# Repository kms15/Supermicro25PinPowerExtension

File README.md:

# Supermicro 25 Pin Power Extension

This project is an extension cable for a Super Micro PWS-1K66P-1R power supply.
This power supply has a 40mm fan which is quite loud, but the design of many
servers does not leave enough space around the power supply to replace this fan
with a larger (and quieter) fan.  The connector on this power supply is a
proprietary 2x25 contact PCB edge connector that carries high (133 Amp)
currents, and thus needs a custom extension cable to move the power supply out
of the case to somewhere with more space.

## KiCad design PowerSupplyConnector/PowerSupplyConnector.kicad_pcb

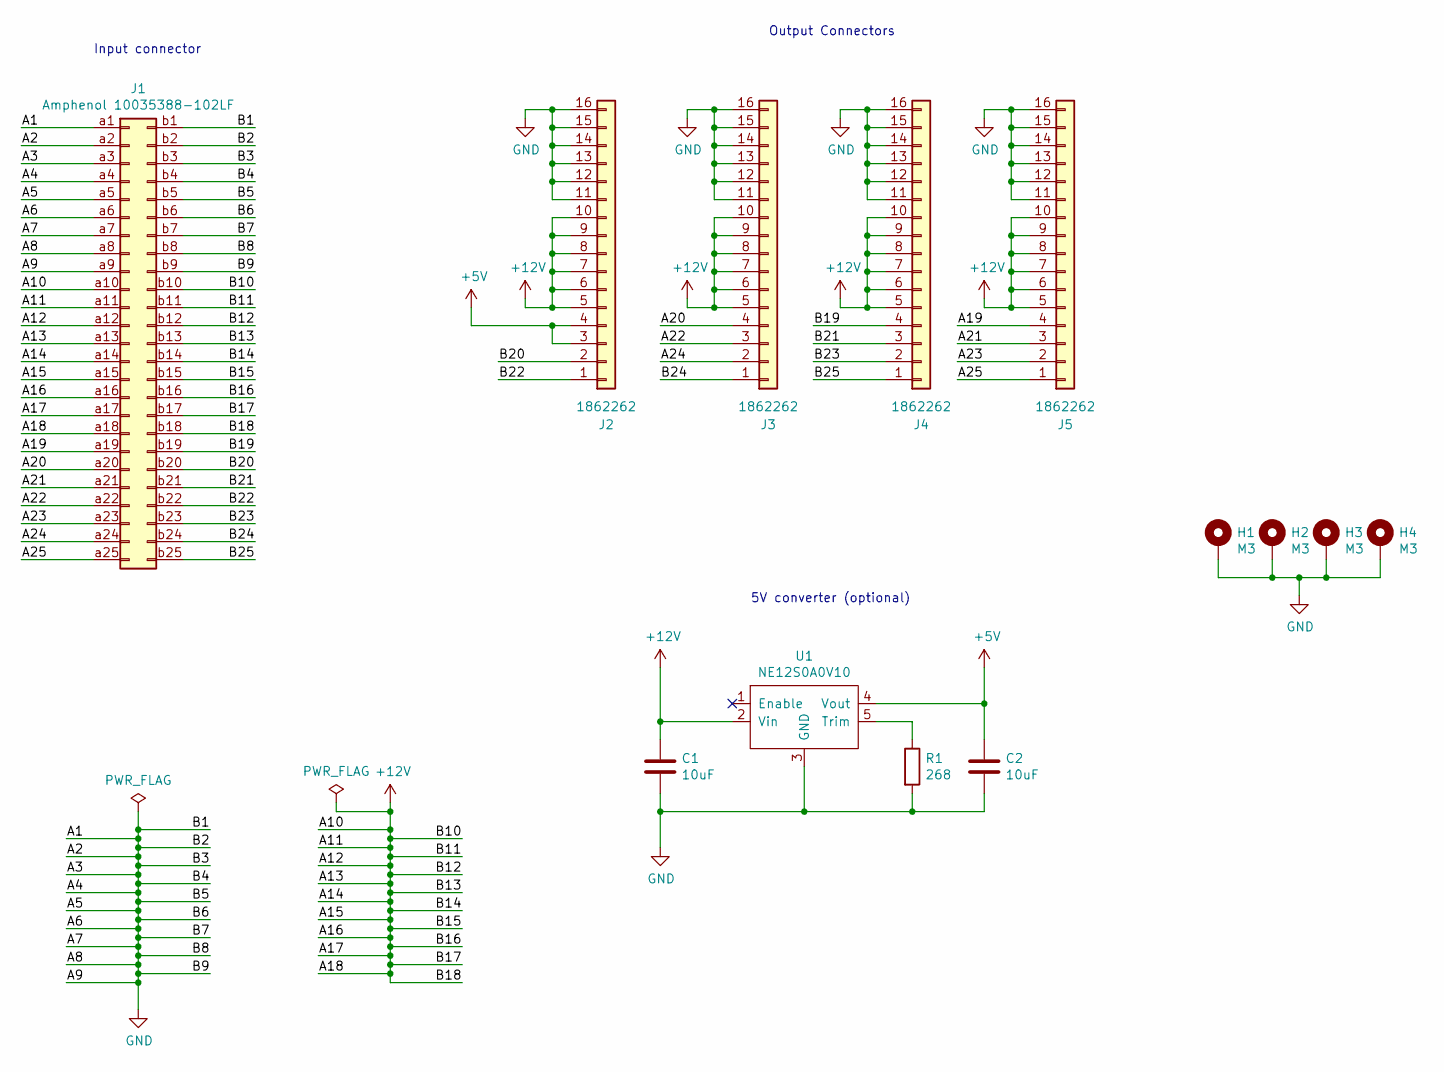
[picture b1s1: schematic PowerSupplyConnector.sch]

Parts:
C1, C2: 10uF; C_0603_1608Metric
H1, H2, H3, H4: M3; MountingHole_3.2mm_M3_Pad
J1: Amphenol 10035388-102LF; Amphenol_10035388-102LF
J2, J3, J4, J5: 1862262; PhoenixContact1862262
R1: 268; R_0603_1608Metric
U1: NE12S0A0V10; Delta_NE12S0A0V10

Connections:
+5V: C2.1, J2.3, J2.4, U1.4 (Vout)
+12V: C1.1, J1.a10, J1.a11, J1.a12, J1.a13, J1.a14, J1.a15, J1.a16, J1.a17, J1.a18, J1.b10, J1.b11, J1.b12, J1.b13, J1.b14, J1.b15, J1.b16, J1.b17, J1.b18, J2.5, J2.6, J2.7, J2.8, J2.9, J2.10, J3.5, J3.6, J3.7, J3.8, J3.9, J3.10, J4.5, J4.6, J4.7, J4.8, J4.9, J4.10, J5.5, J5.6, J5.7, J5.8, J5.9, J5.10, U1.2 (Vin)
/A19: J1.a19, J5.4
/A20: J1.a20, J3.4
/A21: J1.a21, J5.3
/A22: J1.a22, J3.3
/A23: J1.a23, J5.2
/A24: J1.a24, J3.2
/A25: J1.a25, J5.1
/B19: J1.b19, J4.4
/B20: J1.b20, J2.2
/B21: J1.b21, J4.3
/B22: J1.b22, J2.1
/B23: J1.b23, J4.2
/B24: J1.b24, J3.1
/B25: J1.b25, J4.1
GND: C1.2, C2.2, H1.1, H2.1, H3.1, H4.1, J1.a1, J1.a2, J1.a3, J1.a4, J1.a5, J1.a6, J1.a7, J1.a8, J1.a9, J1.b1, J1.b2, J1.b3, J1.b4, J1.b5, J1.b6, J1.b7, J1.b8, J1.b9, J2.11, J2.12, J2.13, J2.14, J2.15, J2.16, J3.11, J3.12, J3.13, J3.14, J3.15, J3.16, J4.11, J4.12, J4.13, J4.14, J4.15, J4.16, J5.11, J5.12, J5.13, J5.14, J5.15, J5.16, R1.2, U1.3 (GND)
unnamed: R1.1, U1.5 (Trim)

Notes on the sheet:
Input connector
Output Connectors
5V converter (optional)

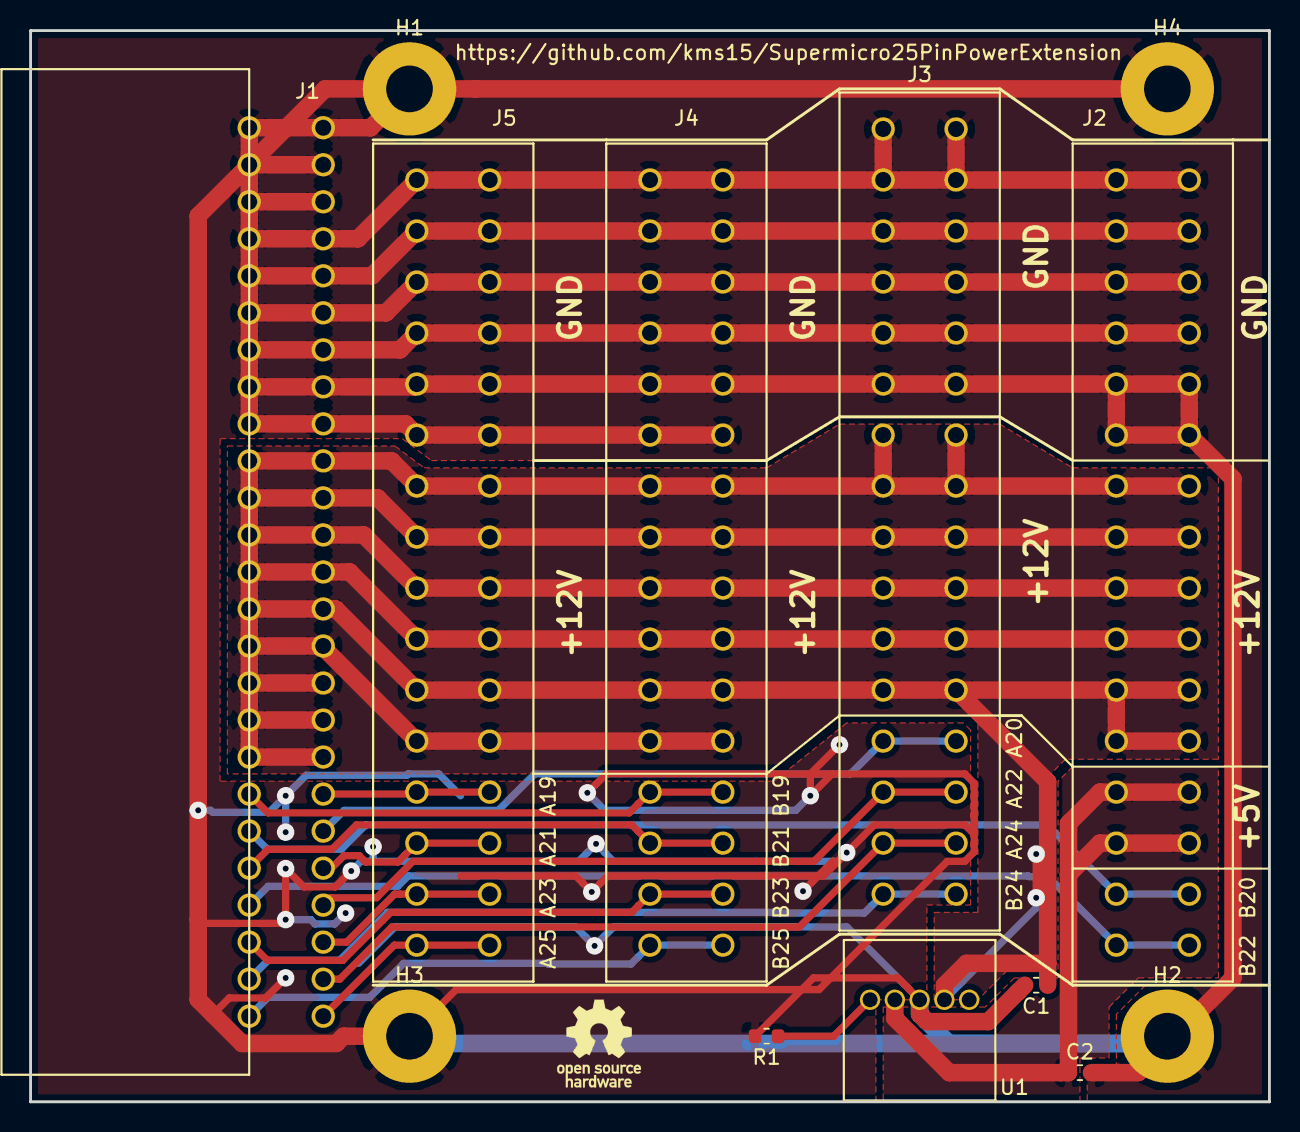
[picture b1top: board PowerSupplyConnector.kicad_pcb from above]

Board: 2 copper layers, 85.0 x 73.5 mm, 13 parts (0 on the bottom side), 18 nets.

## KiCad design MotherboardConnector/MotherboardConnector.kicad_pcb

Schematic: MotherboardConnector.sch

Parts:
C1, C2: 10uF; C_0603_1608Metric
H1, H2, H3, H4: MountingHole_Pad; MountingHole_3.2mm_M3_Pad
J1: Amphenol 10035388-102LF PCB edge; Amphenol_10035388-102LF_PCB_Edge
J2, J3, J4, J5: 1862262; PhoenixContact1862262
R1: 268; R_0603_1608Metric
U1: NE12S0A0V10PNF; Delta_NE12S0A0V10

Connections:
+5V: C2.1, J2.13, J2.14, U1.4
+12V: C1.1, J1.a10, J1.a11, J1.a12, J1.a13, J1.a14, J1.a15, J1.a16, J1.a17, J1.a18, J1.b10, J1.b11, J1.b12, J1.b13, J1.b14, J1.b15, J1.b16, J1.b17, J1.b18, J2.7, J2.8, J2.9, J2.10, J2.11, J2.12, J3.7, J3.8, J3.9, J3.10, J3.11, J3.12, J4.7, J4.8, J4.9, J4.10, J4.11, J4.12, J5.7, J5.8, J5.9, J5.10, J5.11, J5.12, U1.2
/A19: J1.a19, J5.13
/A20: J1.a20, J3.13
/A21: J1.a21, J5.14
/A22: J1.a22, J3.14
/A23: J1.a23, J5.15
/A24: J1.a24, J3.15
/A25: J1.a25, J5.16
/B19: J1.b19, J4.13
/B20: J1.b20, J2.15
/B21: J1.b21, J4.14
/B22: J1.b22, J2.16
/B23: J1.b23, J4.15
/B24: J1.b24, J3.16
/B25: J1.b25, J4.16
GND: C1.2, C2.2, H1.1, H2.1, H3.1, H4.1, J1.a1, J1.a2, J1.a3, J1.a4, J1.a5, J1.a6, J1.a7, J1.a8, J1.a9, J1.b1, J1.b2, J1.b3, J1.b4, J1.b5, J1.b6, J1.b7, J1.b8, J1.b9, J2.1, J2.2, J2.3, J2.4, J2.5, J2.6, J3.1, J3.2, J3.3, J3.4, J3.5, J3.6, J4.1, J4.2, J4.3, J4.4, J4.5, J4.6, J5.1, J5.2, J5.3, J5.4, J5.5, J5.6, R1.2, U1.3
unnamed: R1.1, U1.5

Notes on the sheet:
Output connector
Input Connectors
5V converter (optional)

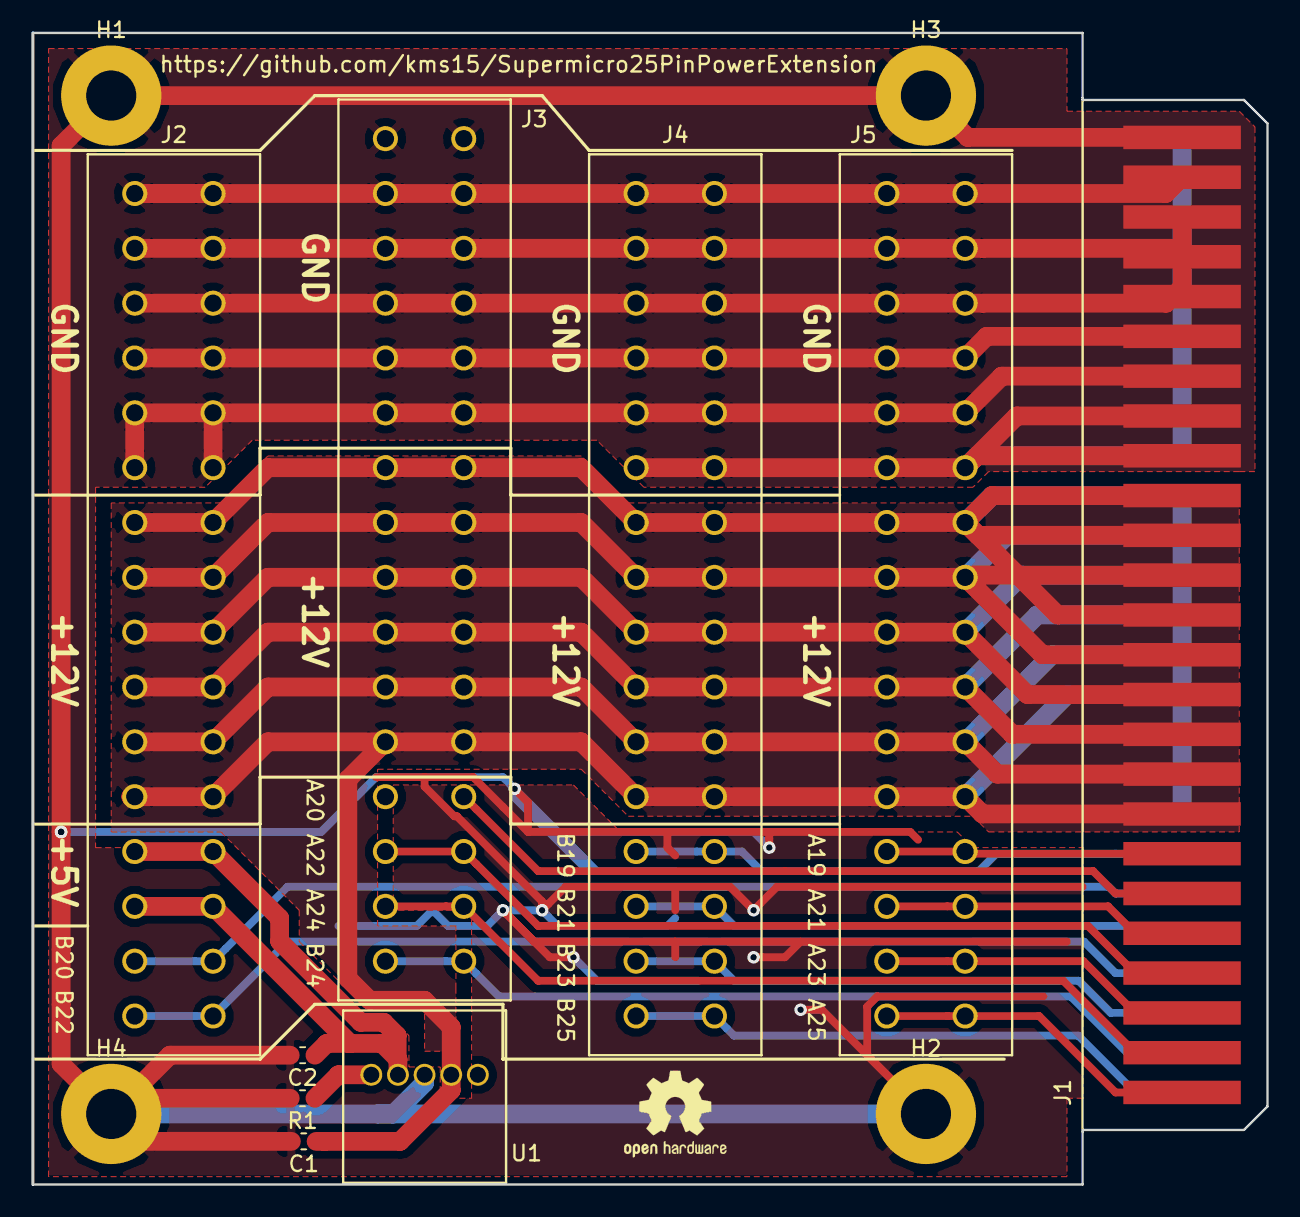
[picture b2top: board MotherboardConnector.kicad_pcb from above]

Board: 2 copper layers, 78.8 x 73.5 mm, 13 parts (0 on the bottom side), 18 nets.

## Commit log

2018-12-09 add .gitignore
2018-12-09 add initial kicad schematics
2018-12-10 added PCB edge connector
2018-12-10 add remaining footprints
2018-12-13 remove soldermask from edge connector
2018-12-13 change to terminal block connector
2018-12-13 fix symbol path issue
2018-12-17 first draft of pcb for power supply side
2018-12-25 Motherboard connector PCB traces completed
2018-12-26 completed motherboard connector PCB
2018-12-28 checkpoint
2018-12-28 add Panelized PCB layout
2019-02-14 add notes on fan connector in power supply
